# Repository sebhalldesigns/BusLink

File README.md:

# BusLink
CAN Bus Logger &amp; Inteface

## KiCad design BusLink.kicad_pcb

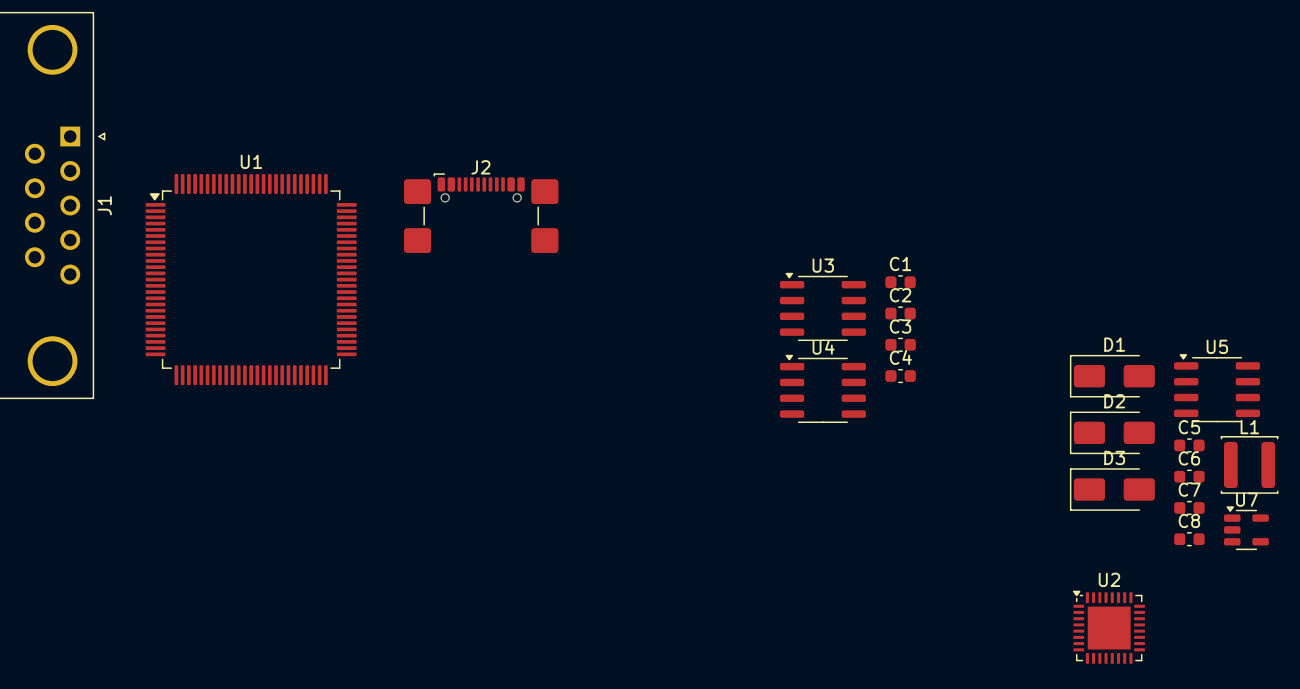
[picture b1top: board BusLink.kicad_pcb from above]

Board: 4 copper layers, 20 parts (0 on the bottom side), 14 nets, no tracks yet.

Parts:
C1, C3: 1u; C_0603_1608Metric
C2, C4: 100n; C_0603_1608Metric
C5: 220uF; C_0603_1608Metric
C6: 470uF; C_0603_1608Metric
C7, C8: 1uF; C_0603_1608Metric
D1, D2, D3: SS14; D_SMA
J1: DE9_Pins; DSUB-9_Pins_Horizontal_P2.77x2.84mm_EdgePinOffset9.90mm_Hou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
J2: USB_C_Receptacle_USB2.0_14P; USB_C_Receptacle_GCT_USB4110
L1: 47uH; L_Sunlord_SWPA4030S
U1: STM32H723VETx; LQFP-100_14x14mm_P0.5mm
U2: USB3300-EZK; QFN-32-1EP_5x5mm_P0.5mm_EP3.45x3.45mm
U3, U4: SN65HVD230; SOIC-8_3.9x4.9mm_P1.27mm
U5: XL1509-3.3; SOIC-8_3.9x4.9mm_P1.27mm
U7: AP2112K-1.8; SOT-23-5

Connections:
+1V8: C7.1, U7.5 (VOUT)
+3V3: C1.1, C2.1, C3.1, C4.1, C5.1, C8.1, L1.2, U3.3 (VCC), U4.3 (VCC), U5.3 (FB), U7.1 (VIN), U7.3 (EN)
+5V: D1.2 (A), J1.1, J2.A4 (VBUS), J2.A9 (VBUS), J2.B4 (VBUS), J2.B9 (VBUS)
+12V: D3.2 (A), J1.9
/CAN0_HI: J1.7, U3.7 (CANH)
/CAN0_LO: J1.2, U3.6 (CANL)
/CAN1_HI: J1.8, U4.7 (CANH)
/CAN1_LO: J1.4, U4.6 (CANL)
/USB/D+: J2.A6 (D+), J2.B6 (D+)
/USB/D-: J2.A7 (D-), J2.B7 (D-)
GND: C1.2, C2.2, C3.2, C4.2, C5.2, C6.2, C7.2, C8.2, D2.2 (A), J1.3, J1.5, J1.6, J2.A1 (GND), J2.A12 (GND), J2.B1 (GND), J2.B12 (GND), J2.S1 (SHIELD), U3.2 (GND), U3.8 (Rs), U4.2 (GND), U4.8 (Rs), U5.4 (~EN), U5.5 (GND), U5.6 (GND), U5.7 (GND), U5.8 (GND), U7.2 (GND)
unnamed: C6.1, D1.1 (K), D3.1 (K), U5.1 (VIN)
unnamed: D2.1 (K), L1.1, U5.2 (OUT)
unnamed: U1.10 (VSS), U1.26 (VSS), U1.49 (VSS), U1.74 (VSS), U1.99 (VSS)

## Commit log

2025-10-13 initial components and project setup
2025-10-16 setting up heirarchy
2025-10-20 working on power supplies and CAN
2025-10-20 removed power supplies
2025-10-20 added inductor selection
